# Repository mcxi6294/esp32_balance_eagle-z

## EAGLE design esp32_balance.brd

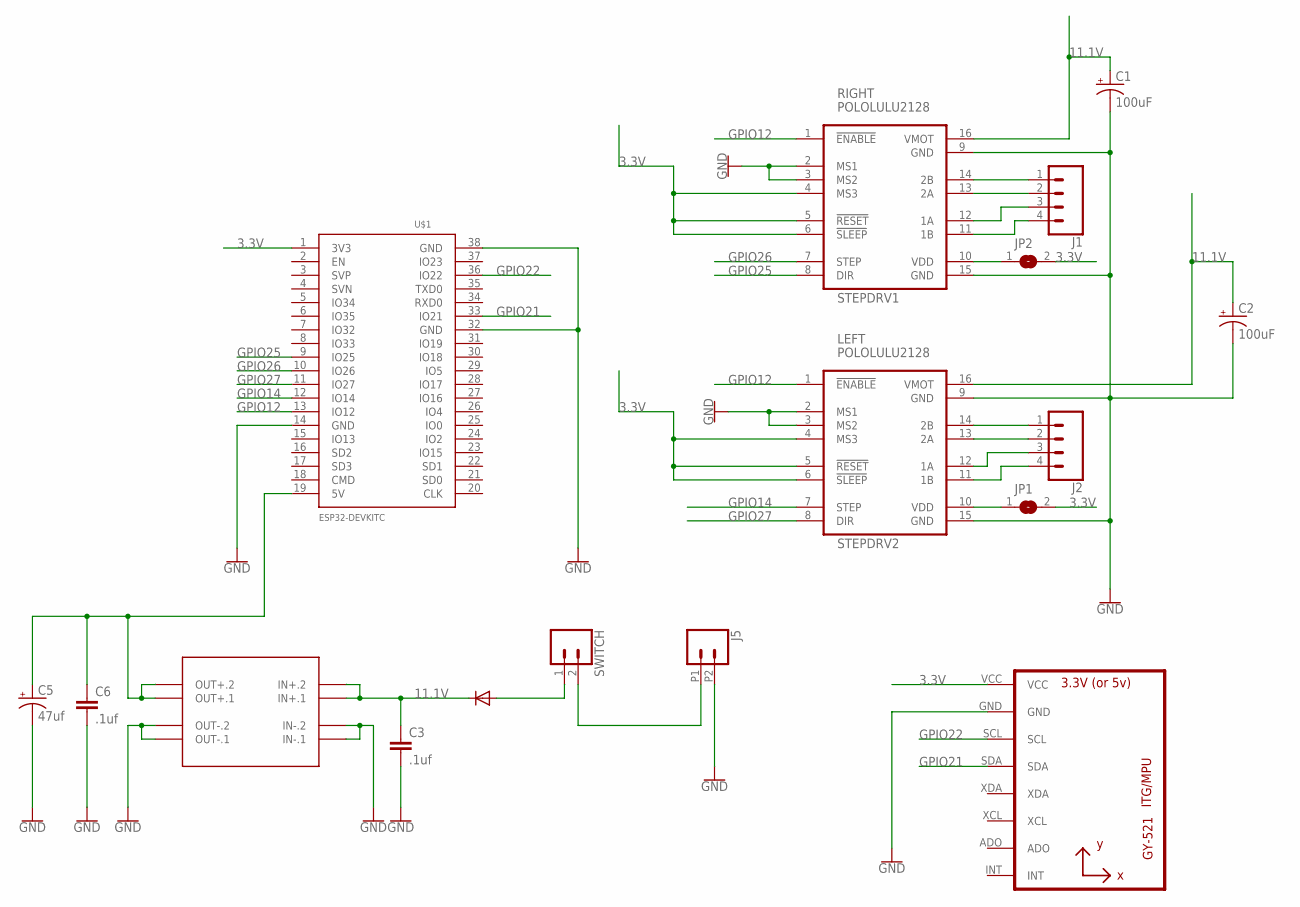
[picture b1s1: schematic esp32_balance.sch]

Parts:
C1, C2: 100uF; CPOL-RADIAL-2.5MM-6.5MM
C3, C6: .1uf; CAP-PTH-2.54
C5: 47uf; CPOL-RADIAL-2.5MM-6.5MM
D1: 1N4004; DO41-10
J1, J2: CONN_04; 1X04
J5: CONN_022.54MM_SCREWTERM; 1X02_2.54_SCREWTERM
JP1, JP2: SJW
STEPDRV1, STEPDRV2: POLOLULU2128
SWITCH: CONN_02; 1X02
U1: GY-521MPU6050; GY-521
U$1: ESP32DEVKITC; ESP32-DEVKITC
U$3: DC-DC-STEP-DOWN-MP1584

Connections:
3.3V: JP1.2, JP2.2, STEPDRV1.4 (MS3), STEPDRV1.5 (!RESET), STEPDRV1.6 (!SLEEP), STEPDRV2.4 (MS3), STEPDRV2.5 (!RESET), STEPDRV2.6 (!SLEEP), U1.VCC, U$1.1 (3V3)
11.1V: C1.1 (+), C2.1 (+), C3.1, D1.C, STEPDRV1.16 (VMOT), STEPDRV2.16 (VMOT), U$3.IN+.1, U$3.IN+.2
GND: C1.2 (-), C2.2 (-), C3.2, C5.2 (-), C6.2, J5.P2 (2), STEPDRV1.2 (MS1), STEPDRV1.3 (MS2), STEPDRV1.9 (GND), STEPDRV1.15 (GND), STEPDRV2.2 (MS1), STEPDRV2.3 (MS2), STEPDRV2.9 (GND), STEPDRV2.15 (GND), U1.GND, U$1.14 (GND), U$1.32 (GND), U$1.38 (GND), U$3.IN-.1, U$3.IN-.2, U$3.OUT-.1, U$3.OUT-.2
GPIO12: STEPDRV1.1 (!ENABLE), STEPDRV2.1 (!ENABLE), U$1.13 (IO12)
GPIO14: STEPDRV2.7 (STEP), U$1.12 (IO14)
GPIO21: U1.SDA, U$1.33 (IO21)
GPIO22: U1.SCL, U$1.36 (IO22)
GPIO25: STEPDRV1.8 (DIR), U$1.9 (IO25)
GPIO26: STEPDRV1.7 (STEP), U$1.10 (IO26)
GPIO27: STEPDRV2.8 (DIR), U$1.11 (IO27)
unnamed: J2.4, STEPDRV2.11 (1B)
unnamed: J2.3, STEPDRV2.12 (1A)
unnamed: J2.2, STEPDRV2.13 (2A)
unnamed: J2.1, STEPDRV2.14 (2B)
unnamed: J1.1, STEPDRV1.14 (2B)
unnamed: J1.2, STEPDRV1.13 (2A)
unnamed: J1.4, STEPDRV1.11 (1B)
unnamed: J1.3, STEPDRV1.12 (1A)
unnamed: D1.A, SWITCH.1
unnamed: C5.1 (+), C6.1, U$1.19 (5V), U$3.OUT+.1, U$3.OUT+.2
unnamed: J5.P1 (1), SWITCH.2
unnamed: JP2.1, STEPDRV1.10 (VDD)
unnamed: JP1.1, STEPDRV2.10 (VDD)

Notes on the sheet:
LEFT
RIGHT

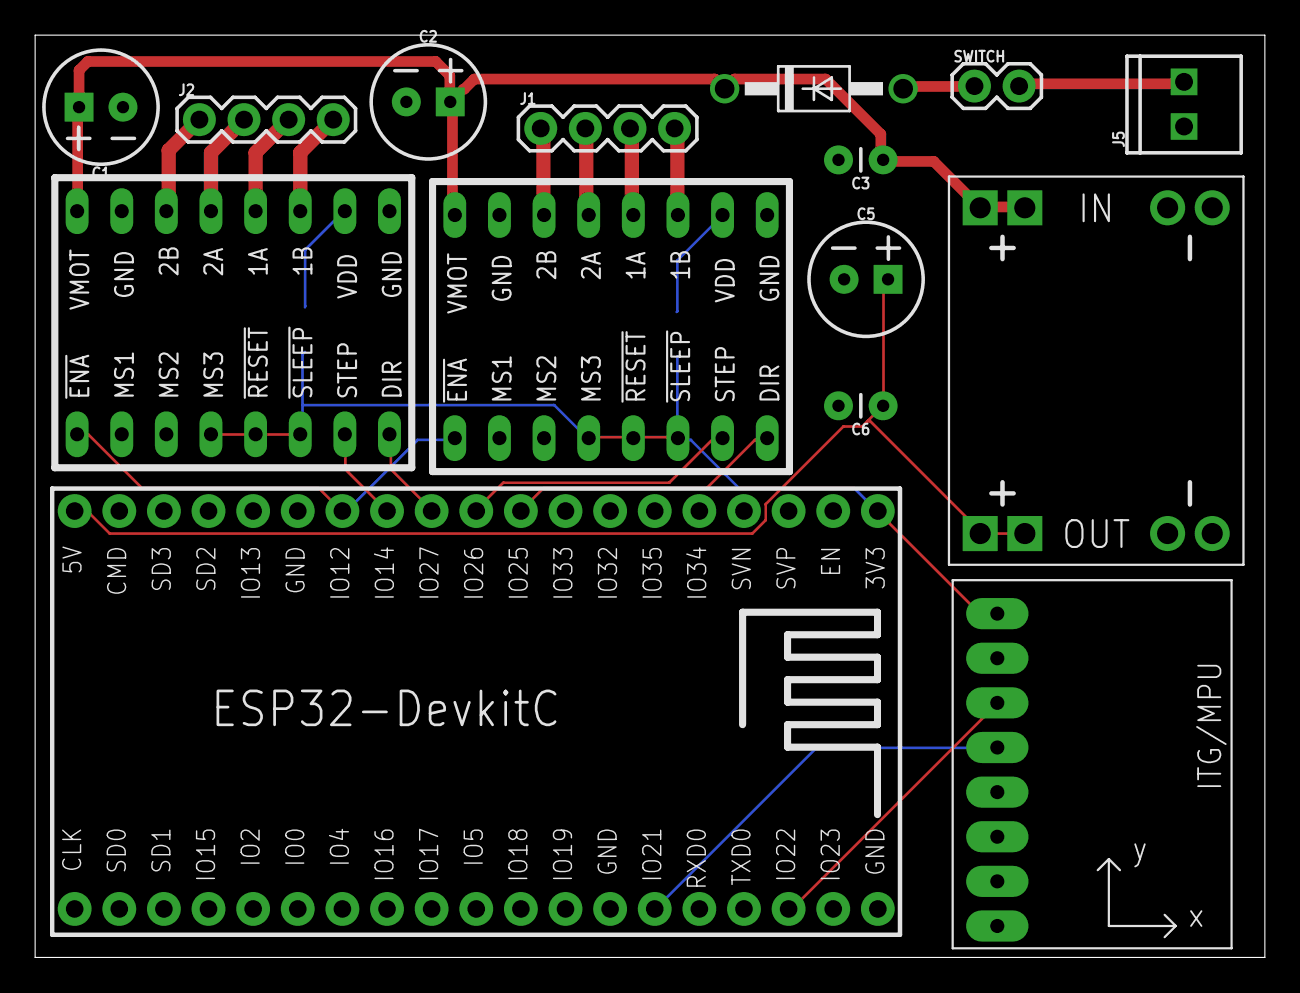
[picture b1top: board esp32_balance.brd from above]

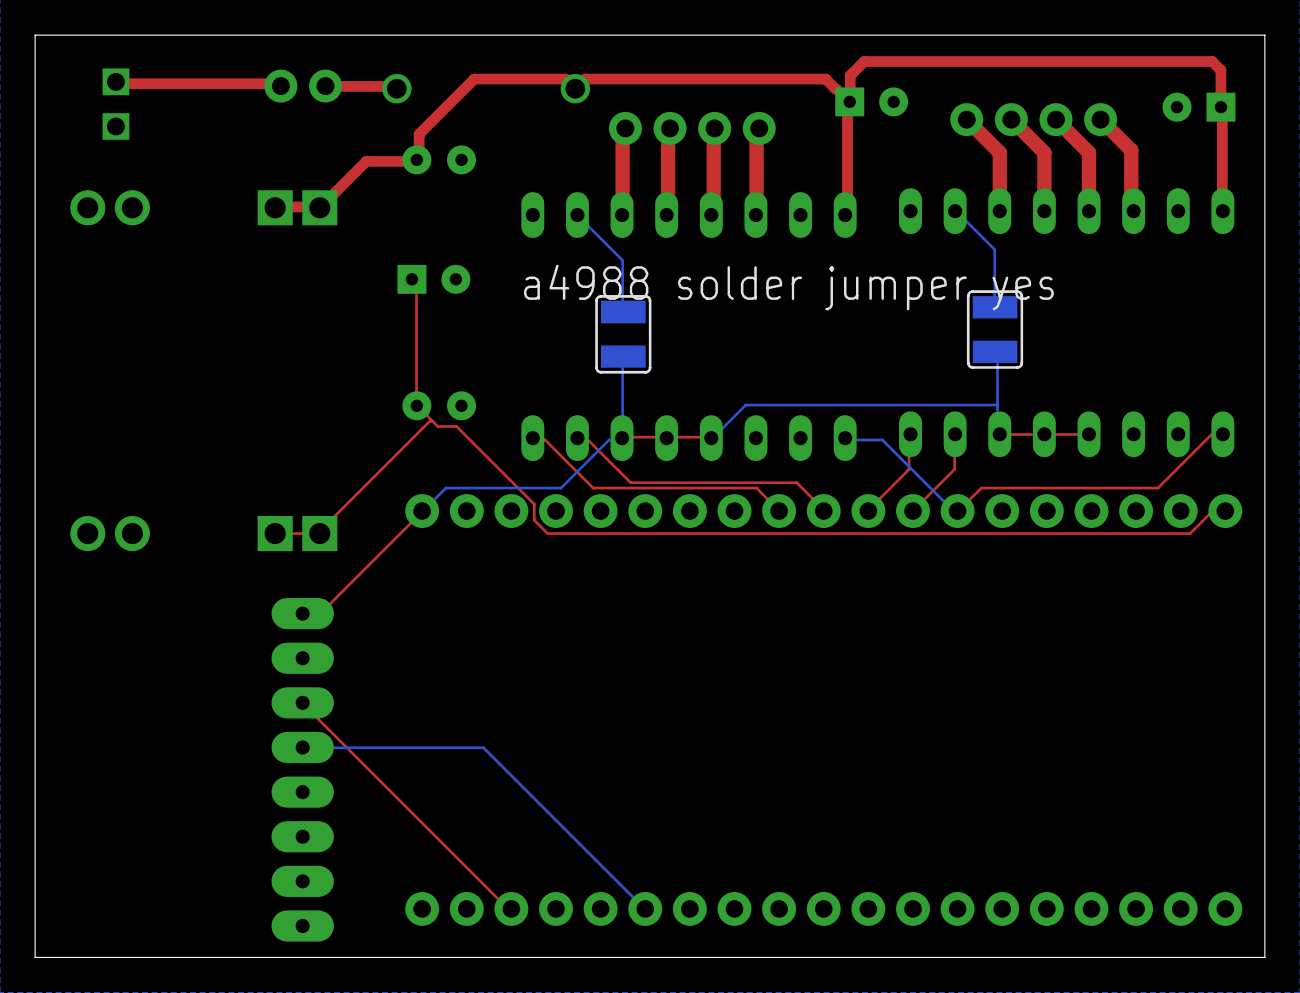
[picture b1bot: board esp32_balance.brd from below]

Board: 2 copper layers, 70.0 x 52.5 mm, 17 parts (2 on the bottom side), 23 nets.

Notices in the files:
parts and their libraries:
SparkFun-Connectors: Licensing: Creative Commons ShareAlike 4.0 International - https://creativecommons.org/licenses/by-sa/4.0
diy-modules: Released under the Creative Commons Attribution 4.0 International License: http://creativecommons.org/licenses/by/4.0
